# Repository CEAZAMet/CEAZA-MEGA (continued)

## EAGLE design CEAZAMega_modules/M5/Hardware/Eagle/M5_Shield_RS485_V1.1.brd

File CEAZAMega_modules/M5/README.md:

# CEAZA-M5
Serial RS-485 interface for wired instruments communication.

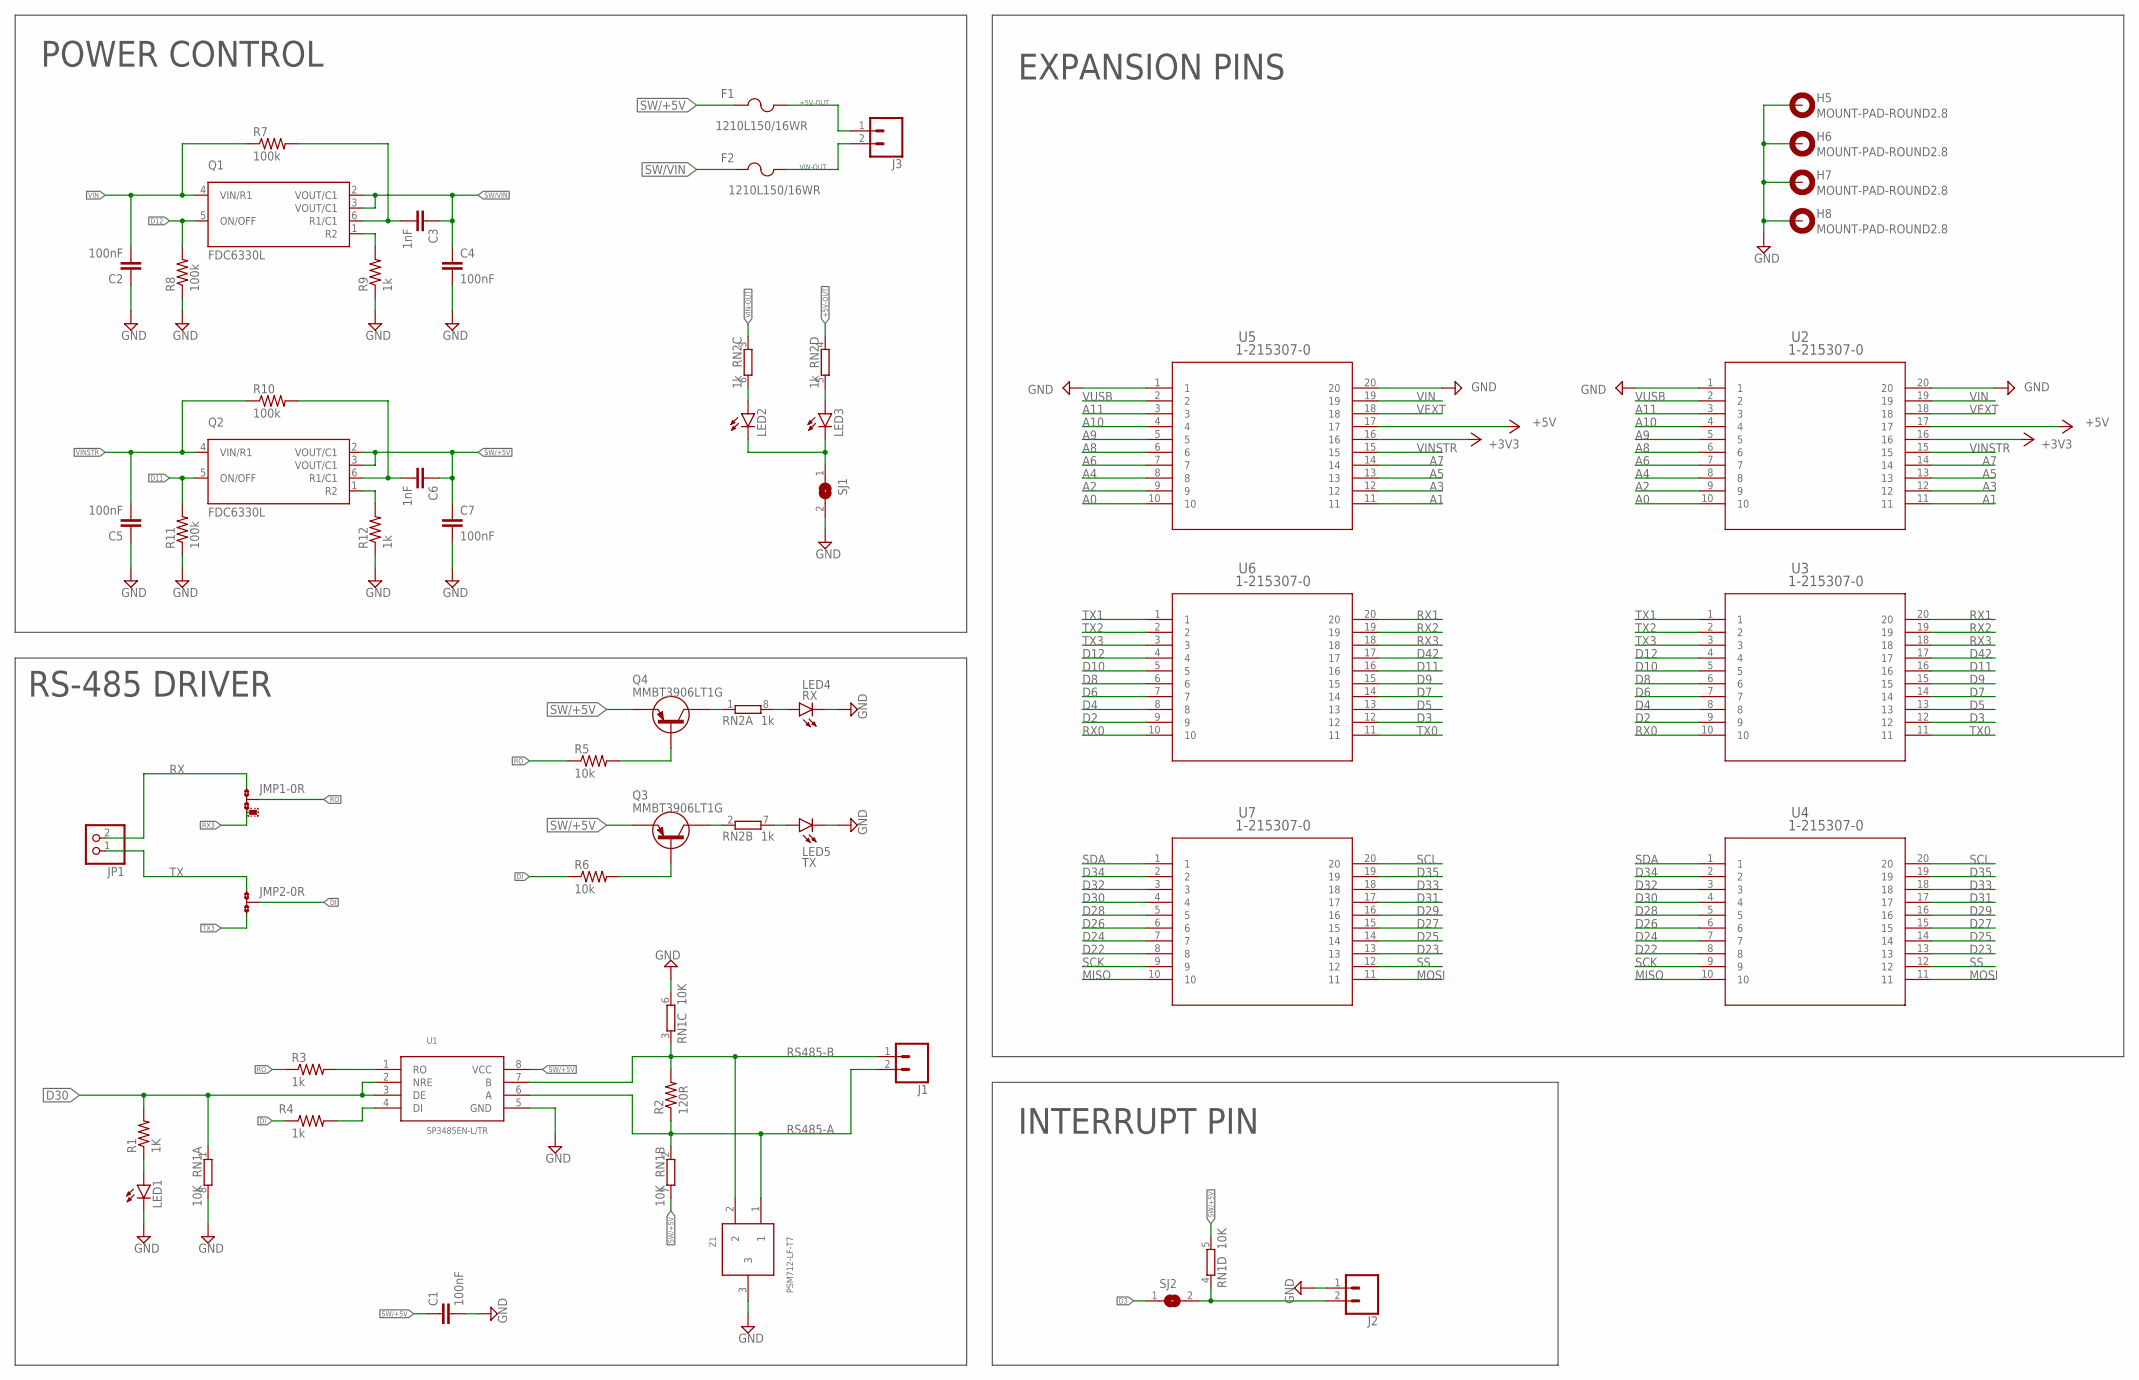
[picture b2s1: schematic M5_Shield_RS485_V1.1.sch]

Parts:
C1: 100nF; C0603K
C2, C4, C5, C7: 100nF; C0603
C3, C6: 1nF; C0603
F1, F2: 1210L150/16WR; 1210LSERIES
H5, H6, H7, H8: MOUNT-PAD-ROUND2.8; 2,8-PAD
J1, J2, J3: CONN_023.5MM; SCREWTERMINAL-3.5MM-2
JMP1, JMP2: 0R-JUMPA; A0R-JMP
JP1: PINHD-1X2; 1X02
LED1: LEDCHIPLED_0603; CHIPLED_0603
LED2, LED3: LEDCHIP-LED0603; CHIP-LED0603
LED4: RX; CHIP-LED0603
LED5: TX; CHIP-LED0603
Q1, Q2: FDC6330L; SOT95P280X110-6N
Q3, Q4: MMBT3906LT1G; SOT23
R1: 1K; R0603
R2: 120R; R0603
R3, R4, R9, R12: 1k; R0603
R5, R6: 10k; R0603
R7, R8, R10, R11: 100k; R0603
RN1: 10K; 0603-ARV
RN2: 1k; 0603-ARV
SJ1, SJ2: SJ
U1: SP3485EN-L/TR
U2, U3, U4, U5, U6, U7: 1-215307-0
Z1: PSM712-LF-T7; SOT23

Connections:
+3V3: U2.16, U5.16
+5V: U2.17, U5.17
+5V-OUT: F1.2, J3.1, RN2.4 (1)
A0: U2.10, U5.10
A1: U2.11, U5.11
A2: U2.9, U5.9
A3: U2.12, U5.12
A4: U2.8, U5.8
A5: U2.13, U5.13
A6: U2.7, U5.7
A7: U2.14, U5.14
A8: U2.6, U5.6
A9: U2.5, U5.5
A10: U2.4, U5.4
A11: U2.3, U5.3
D2: U3.9, U6.9
D3: SJ2.1, U3.12, U6.12
D4: U3.8, U6.8
D5: U3.13, U6.13
D6: U3.7, U6.7
D7: U3.14, U6.14
D8: U3.6, U6.6
D9: U3.15, U6.15
D10: U3.5, U6.5
D11: Q2.5 (ON/OFF), R11.2, U3.16, U6.16
D12: Q1.5 (ON/OFF), R8.2, U3.4, U6.4
D22: U4.8, U7.8
D23: U4.13, U7.13
D24: U4.7, U7.7
D25: U4.14, U7.14
D26: U4.6, U7.6
D27: U4.15, U7.15
D28: U4.5, U7.5
D29: U4.16, U7.16
D30: R1.2, RN1.1, U1.2 (NRE), U1.3 (DE), U4.4, U7.4
D31: U4.17, U7.17
D32: U4.3, U7.3
D33: U4.18, U7.18
D34: U4.2, U7.2
D35: U4.19, U7.19
D42: U3.17, U6.17
DI: JMP2.2, R4.1, R6.1
GND: C1.2, C2.1, C4.2, C5.1, C7.2, H5.B2,8, H6.B2,8, H7.B2,8, H8.B2,8, J2.1, LED1.C, LED4.C, LED5.C, R8.1, R9.1, R11.1, R12.1, RN1.6 (2), RN1.8 (2), SJ1.2, U1.5 (GND), U2.1, U2.20, U5.1, U5.20, Z1.3
MISO: U4.10, U7.10
MOSI: U4.11, U7.11
unnamed: LED1.A, R1.1
unnamed: R3.2, U1.1 (RO)
unnamed: J2.2, RN1.4 (1), SJ2.2
unnamed: Q4.3 (C), RN2.1
unnamed: R4.2, U1.4 (DI)
unnamed: LED3.A, RN2.5 (2)
unnamed: LED2.C, LED3.C, SJ1.1
unnamed: LED2.A, RN2.6 (2)
unnamed: Q3.3 (C), RN2.2 (1)
unnamed: LED4.A, RN2.8 (2)
unnamed: C6.2, Q2.6 (R1/C1), R10.2
unnamed: Q1.1 (R2), R9.2
unnamed: LED5.A, RN2.7 (2)
unnamed: Q4.1 (B), R5.2
unnamed: C3.2, Q1.6 (R1/C1), R7.2
unnamed: Q3.1 (B), R6.2
unnamed: Q2.1 (R2), R12.2
RO: JMP1.2, R3.1, R5.1
RS485-A: J1.2, R2.1, RN1.2 (1), U1.6 (A), Z1.1
RS485-B: J1.1, R2.2, RN1.3 (1), U1.7 (B), Z1.2
RX: JMP1.1, JP1.2
RX0: U3.10, U6.10
RX1: U3.20, U6.20
RX2: U3.19, U6.19
RX3: JMP1.3, U3.18, U6.18
SCK: U4.9, U7.9
SCL: U4.20, U7.20
SDA: U4.1, U7.1
SS: U4.12, U7.12
SW/+5V: C1.1, C6.1, C7.1, F1.1, Q2.2 (VOUT/C1), Q2.3 (VOUT/C1), Q3.2 (E), Q4.2 (E), RN1.5 (2), RN1.7 (2), U1.8 (VCC)
SW/VIN: C3.1, C4.1, F2.1, Q1.2 (VOUT/C1), Q1.3 (VOUT/C1)
TX: JMP2.1, JP1.1
TX0: U3.11, U6.11
TX1: U3.1, U6.1
TX2: U3.2, U6.2
TX3: JMP2.3, U3.3, U6.3
VEXT: U2.18, U5.18
VIN: C2.2, Q1.4 (VIN/R1), R7.1, U2.19, U5.19
VIN-OUT: F2.2, J3.2, RN2.3 (1)
VINSTR: C5.2, Q2.4 (VIN/R1), R10.1, U2.15, U5.15
VUSB: U2.2, U5.2

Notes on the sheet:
RS-485 DRIVER
POWER CONTROL
EXPANSION PINS
INTERRUPT PIN

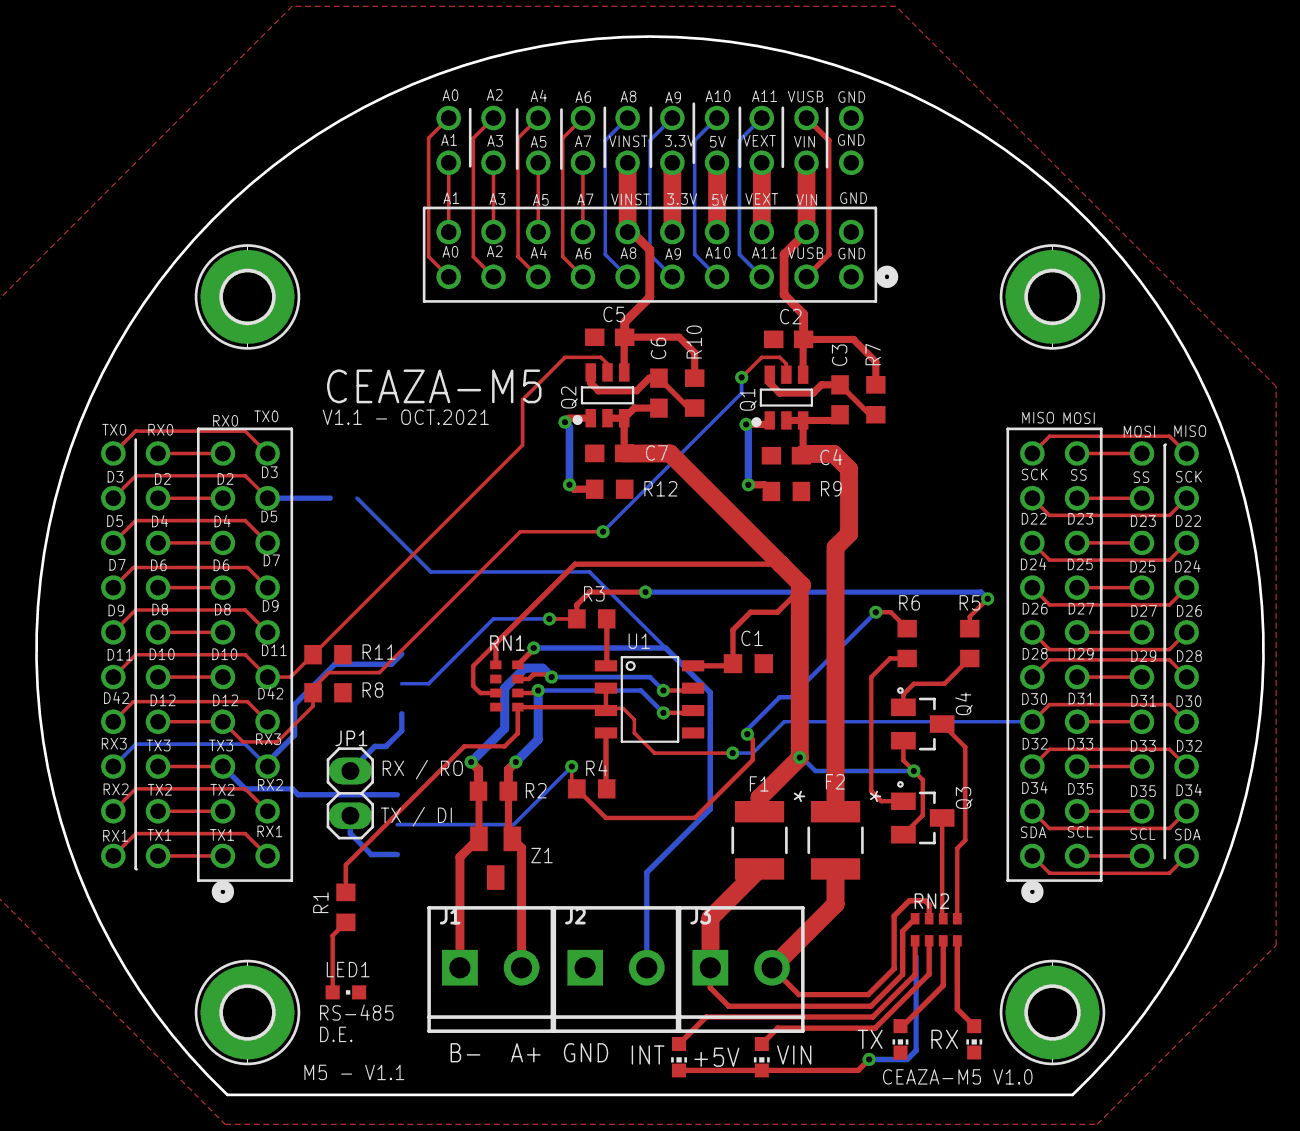
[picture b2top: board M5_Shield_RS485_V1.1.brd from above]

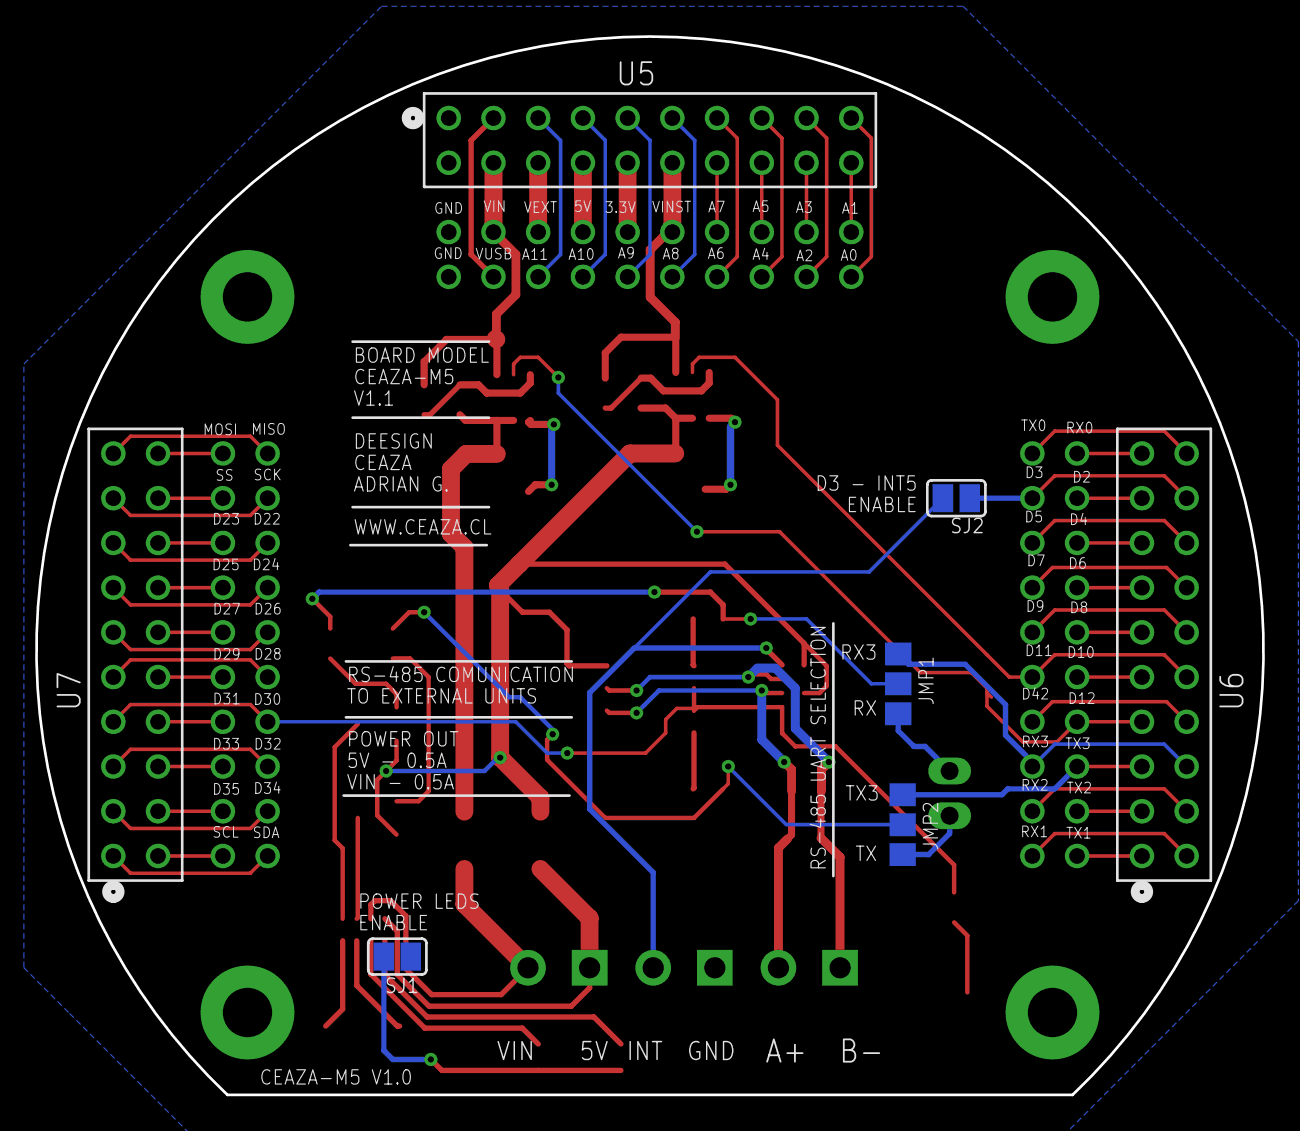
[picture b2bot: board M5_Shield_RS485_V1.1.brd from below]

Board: 2 copper layers, 69.7 x 60.1 mm, 52 parts (7 on the bottom side), 86 nets.

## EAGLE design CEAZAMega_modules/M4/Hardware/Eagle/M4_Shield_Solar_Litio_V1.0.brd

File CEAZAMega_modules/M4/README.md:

# CEAZA-M4
Solar charger for 3.7V lithium battery in CEAZA MEGA system.

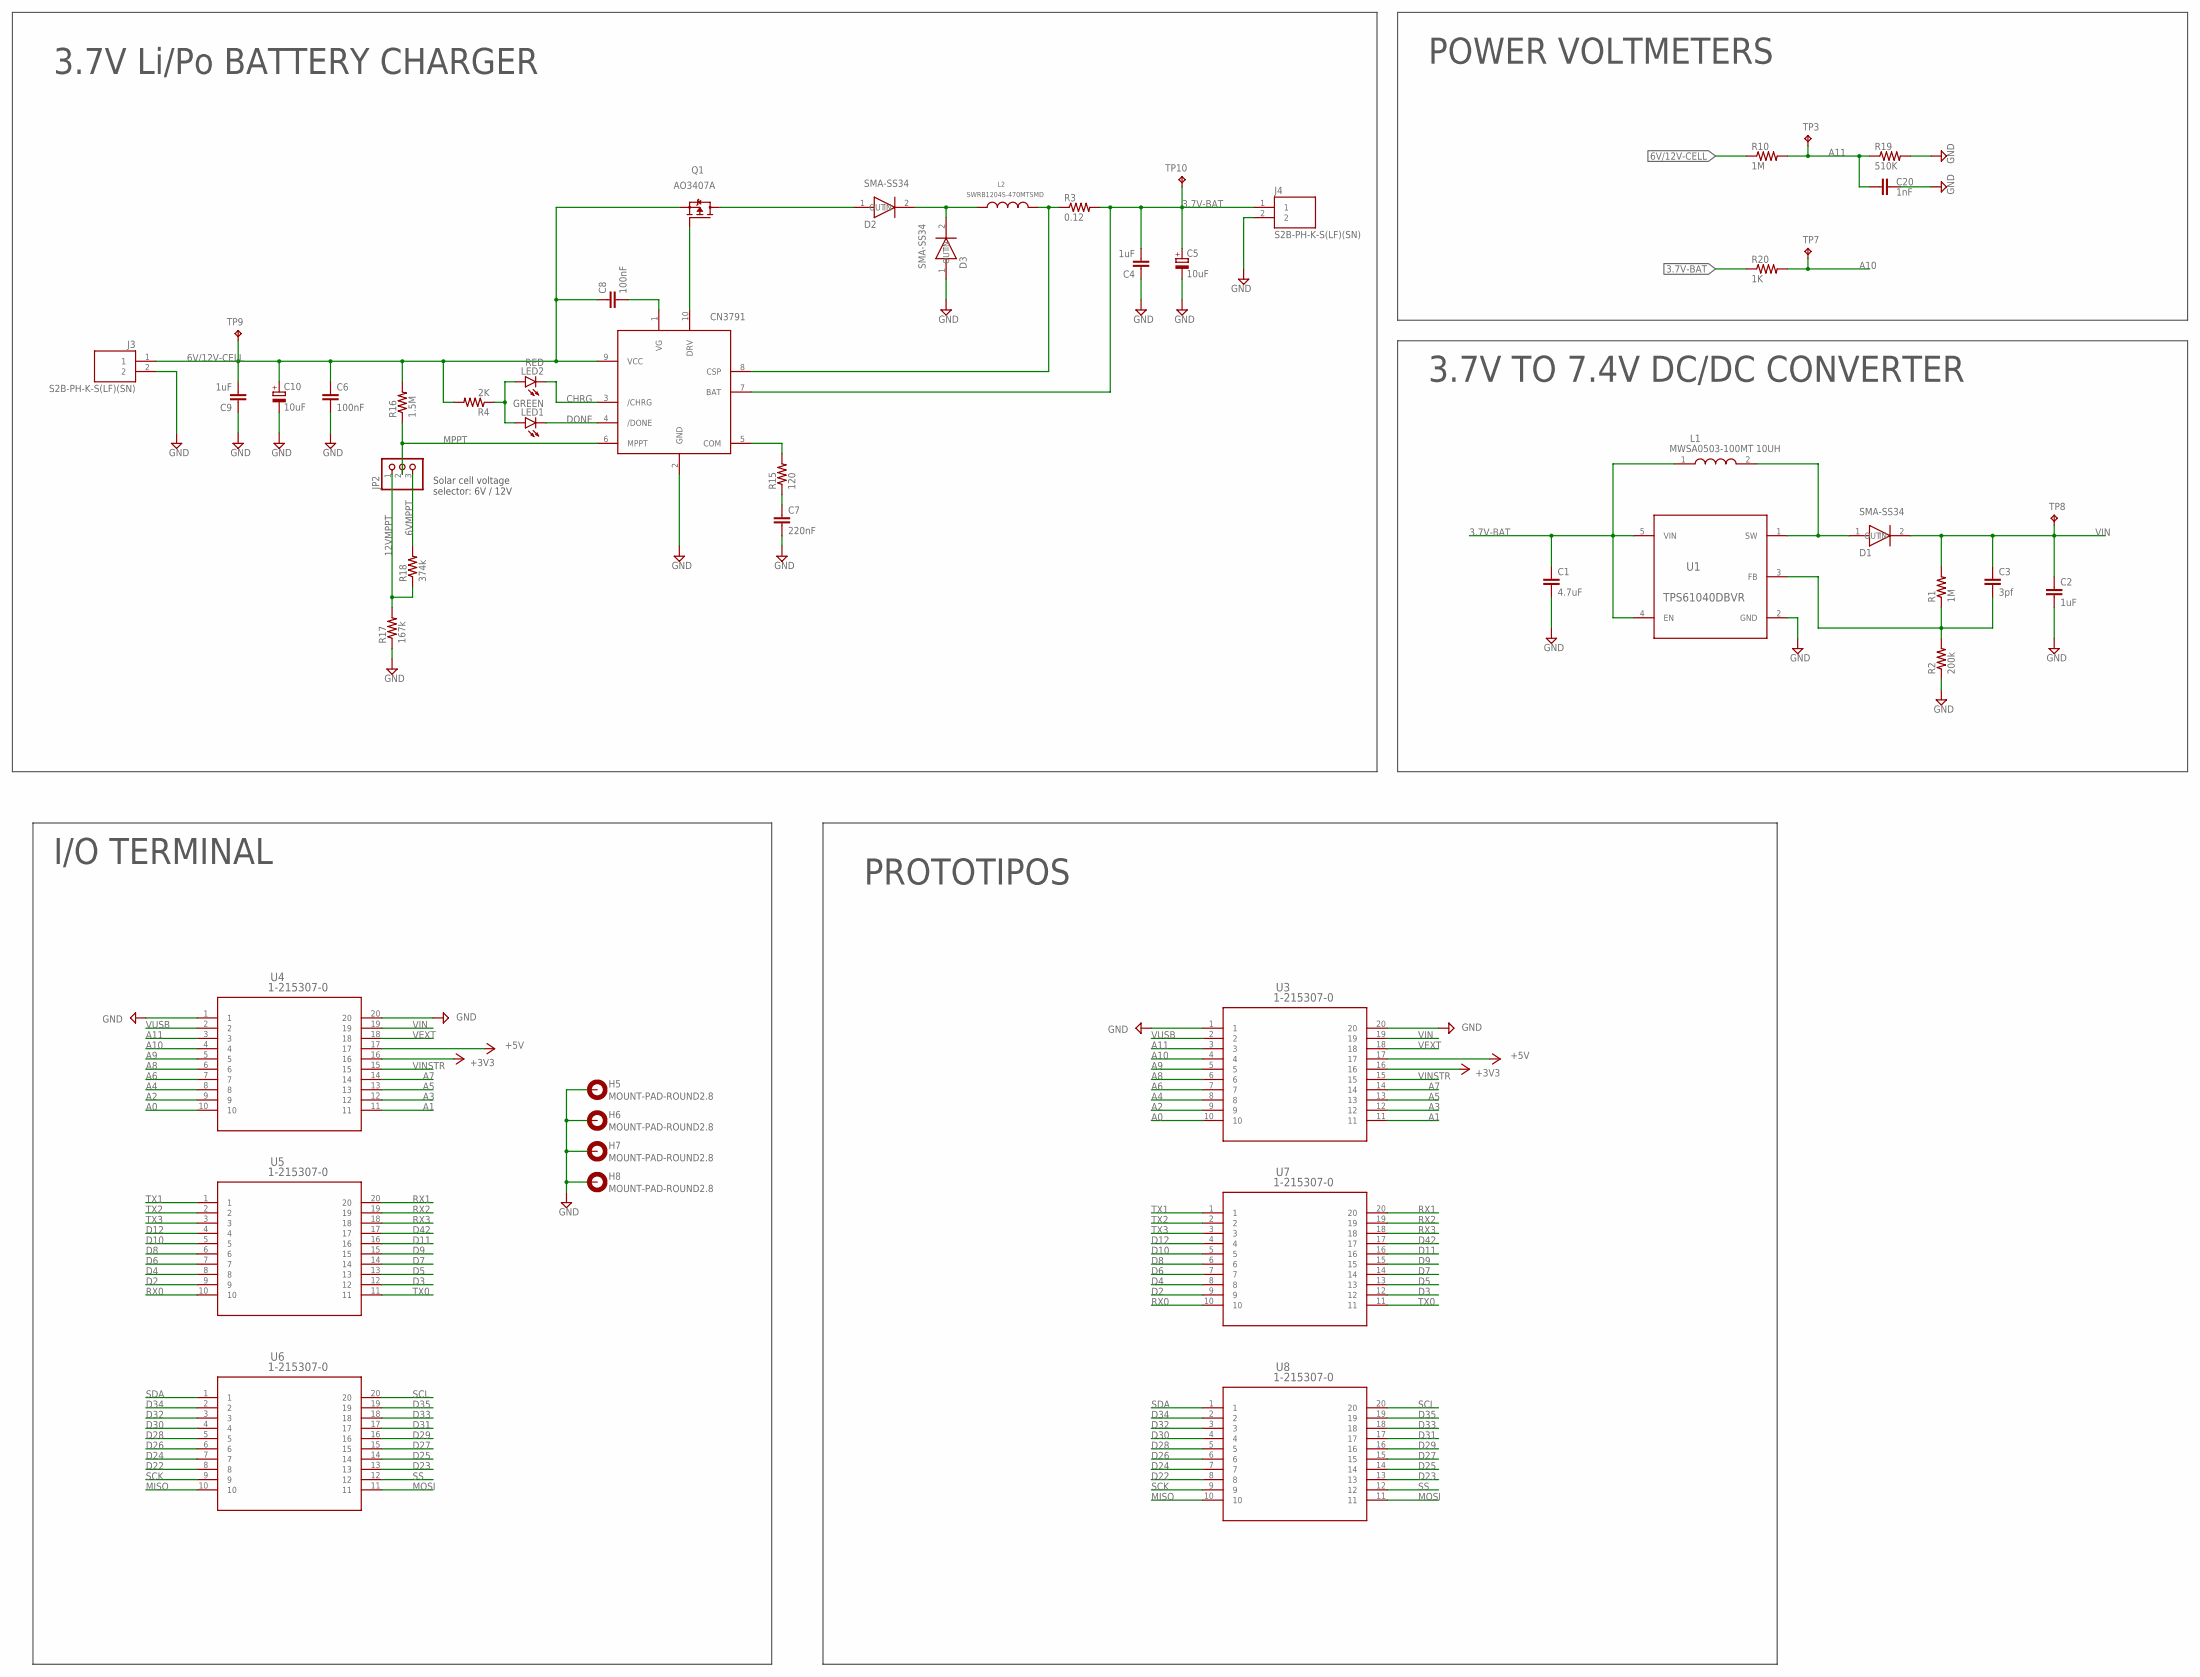
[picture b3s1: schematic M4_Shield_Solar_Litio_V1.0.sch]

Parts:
C1: 4.7uF; C0603K
C2, C4, C9: 1uF; C0603K
C3: 3pf; C0603K
C5, C10: 10uF; 153CLV-0505
C6, C8: 100nF; C0603K
C7: 220nF; C0603K
C20: 1nF; C0603K
D1, D2, D3: SMA-SS34
H5, H6, H7, H8: MOUNT-PAD-ROUND2.8; 2,8-PAD
J3, J4: S2B-PH-K-S(LF)(SN); JST_S2B-PH-K-S(LF)(SN)
JP2: PINHD-1X3/90; 1X03/90
L1: MWSA0503-100MT 10UH; MWSA0503
L2: SWRB1204S-470MTSMD; SWRB1204S-470MT
LED1: GREEN; CHIPLED_0603
LED2: RED; CHIPLED_0603
Q1: AO3407A; SOT95P280X125-3N
R1, R10: 1M; R0603
R2: 200k; R0603
R3: 0.12; R0805
R4: 2K; R0603
R15: 120; R0603
R16: 1.5M; R0603
R17: 167k; R0603
R18: 374k; R0603
R19: 510K; R0603
R20: 1K; R0603
TP3, TP7, TP8, TP9, TP10: TPB1,27; B1,27
U1: TPS61040DBVR; DBV0005A
U2: CN3791
U3, U4, U5, U6, U7, U8: 1-215307-0

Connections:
3.7V-BAT: C1.1, C4.2, C5.+, J4.1, L1.1, R3.2, R20.1, TP10.TP, U1.4 (EN), U1.5 (VIN), U2.7 (BAT)
6V/12V-CELL: C6.1, C8.1, C9.2, C10.+, J3.1, Q1.2 (S), R4.2, R10.1, R16.2, TP9.TP, U2.9 (VCC)
6VMPPT: JP2.3, R18.2
12VMPPT: JP2.1, R17.2, R18.1
+3V3: U3.16, U4.16
+5V: U3.17, U4.17
A0: U3.10, U4.10
A1: U3.11, U4.11
A2: U3.9, U4.9
A3: U3.12, U4.12
A4: U3.8, U4.8
A5: U3.13, U4.13
A6: U3.7, U4.7
A7: U3.14, U4.14
A8: U3.6, U4.6
A9: U3.5, U4.5
A10: R20.2, TP7.TP, U3.4, U4.4
A11: C20.1, R10.2, R19.1, TP3.TP, U3.3, U4.3
CHRG: LED2.C, U2.3 (/CHRG)
D2: U5.9, U7.9
D3: U5.12, U7.12
D4: U5.8, U7.8
D5: U5.13, U7.13
D6: U5.7, U7.7
D7: U5.14, U7.14
D8: U5.6, U7.6
D9: U5.15, U7.15
D10: U5.5, U7.5
D11: U5.16, U7.16
D12: U5.4, U7.4
D22: U6.8, U8.8
D23: U6.13, U8.13
D24: U6.7, U8.7
D25: U6.14, U8.14
D26: U6.6, U8.6
D27: U6.15, U8.15
D28: U6.5, U8.5
D29: U6.16, U8.16
D30: U6.4, U8.4
D31: U6.17, U8.17
D32: U6.3, U8.3
D33: U6.18, U8.18
D34: U6.2, U8.2
D35: U6.19, U8.19
D42: U5.17, U7.17
DONE: LED1.C, U2.4 (/DONE)
GND: C1.2, C2.2, C4.1, C5.-, C6.2, C7.2, C9.1, C10.-, C20.2, D3.1 (IN), H5.B2,8, H6.B2,8, H7.B2,8, H8.B2,8, J3.2, J4.2, R2.1, R17.1, R19.2, U1.2 (GND), U2.2 (GND), U3.1, U3.20, U4.1, U4.20
MISO: U6.10, U8.10
MOSI: U6.11, U8.11
MPPT: JP2.2, R16.1, U2.6 (MPPT)
unnamed: D1.1 (IN), L1.2, U1.1 (SW)
unnamed: D2.2 (OUT), D3.2 (OUT), L2.1
unnamed: C3.2, R1.1, R2.2, U1.3 (FB)
unnamed: L2.2, R3.1, U2.8 (CSP)
unnamed: R15.2, U2.5 (COM)
unnamed: D2.1 (IN), Q1.3 (D)
unnamed: Q1.1 (G), U2.10 (DRV)
unnamed: LED1.A, LED2.A, R4.1
unnamed: C7.1, R15.1
unnamed: C8.2, U2.1 (VG)
RX0: U5.10, U7.10
RX1: U5.20, U7.20
RX2: U5.19, U7.19
RX3: U5.18, U7.18
SCK: U6.9, U8.9
SCL: U6.20, U8.20
SDA: U6.1, U8.1
SS: U6.12, U8.12
TX0: U5.11, U7.11
TX1: U5.1, U7.1
TX2: U5.2, U7.2
TX3: U5.3, U7.3
VEXT: U3.18, U4.18
VIN: C2.1, C3.1, D1.2 (OUT), R1.2, TP8.TP, U3.19, U4.19
VINSTR: U3.15, U4.15
VUSB: U3.2, U4.2

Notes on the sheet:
3.7V Li/Po BATTERY CHARGER
Solar cell voltage selector: 6V / 12V
3.7V TO 7.4V DC/DC CONVERTER
POWER VOLTMETERS
I/O TERMINAL
PROTOTIPOS

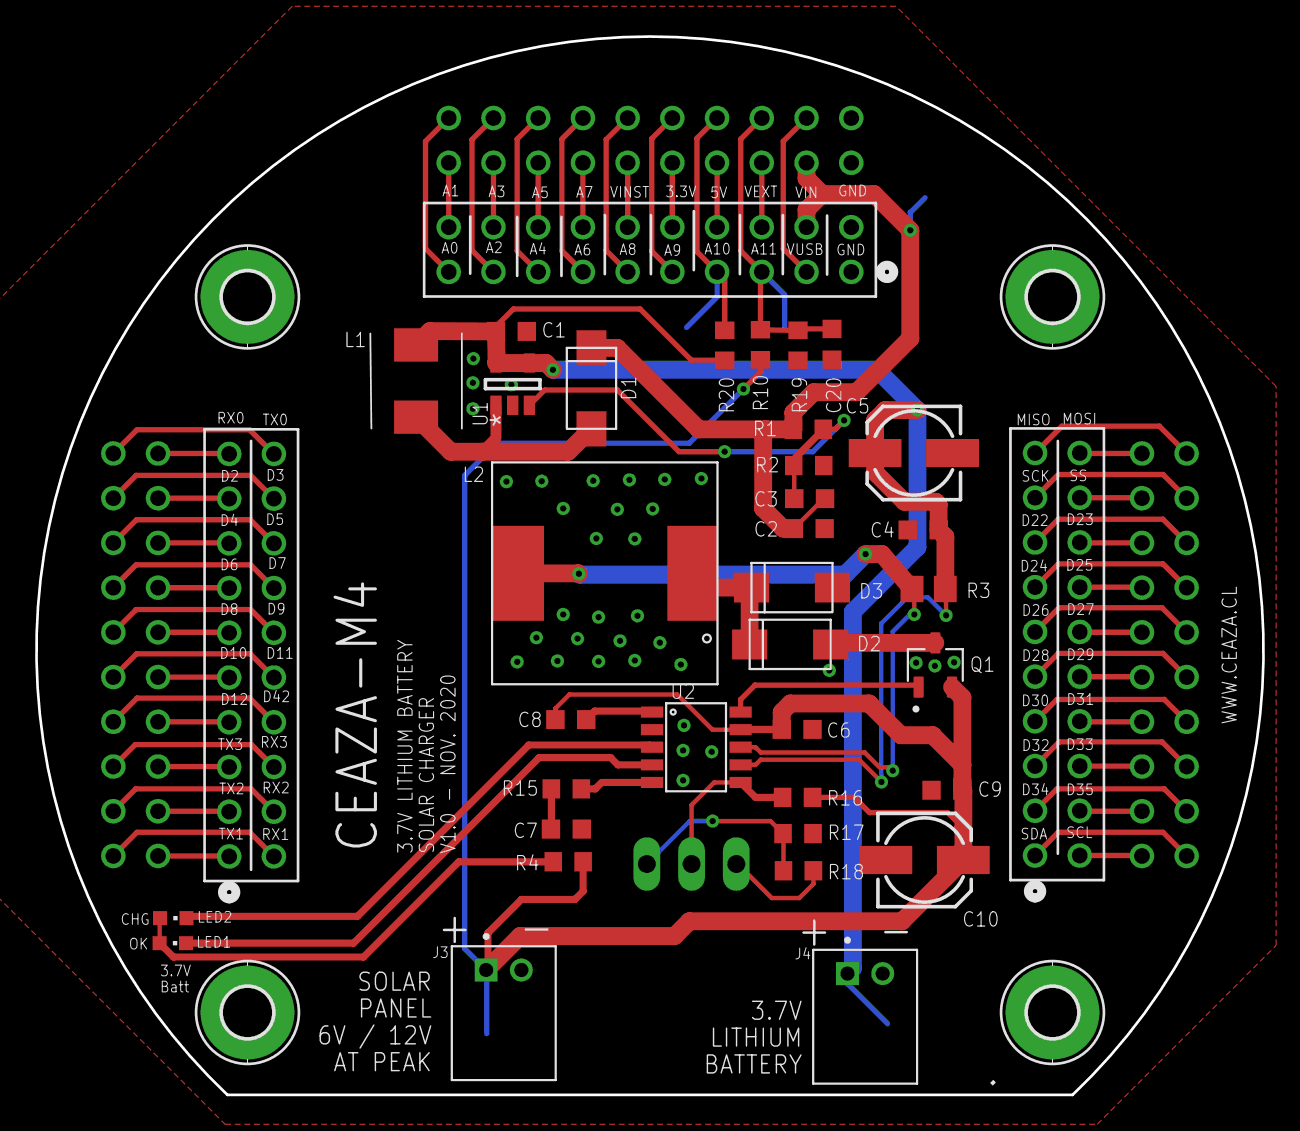
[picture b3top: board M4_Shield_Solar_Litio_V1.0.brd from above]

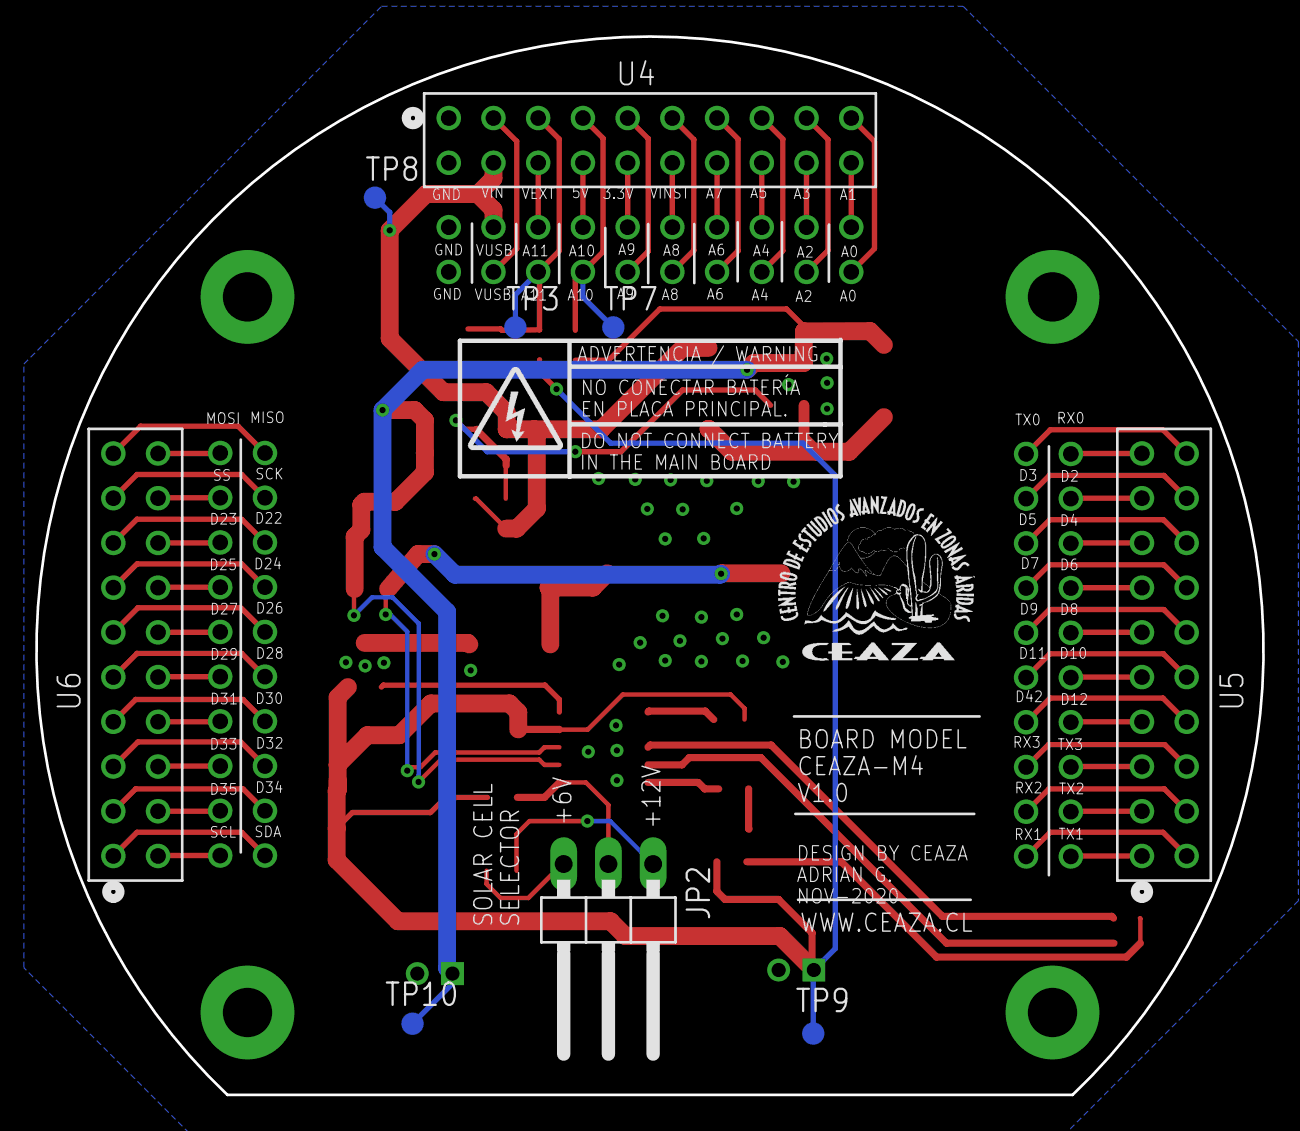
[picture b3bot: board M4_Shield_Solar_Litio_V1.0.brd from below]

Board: 2 copper layers, 69.7 x 60.1 mm, 50 parts (9 on the bottom side), 76 nets.
